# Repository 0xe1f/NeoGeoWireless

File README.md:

NeoGeoWireless
====

NeoGeoWireless is a wireless Neo Geo controller, built on top of a cheap
aftermarket 2.4 GHz SNES Controller.  
It works by converting the SNES controller signals (that would normally go to
the SNES) to format compatible with Neo-Geo, in the process adding features,
like Turbo and Macro button support.

## Requirements

[2.4GHz SNES Controller](https://www.amazon.com/gp/product/B09H4826RV/)  
3x 0.1uF Capacitors  
LED (to display turbo status)  
Atmega328P  
Neo-Geo controller DIN connector, hopefully cannibalized from NG Controller
extension cords  
Custom PCB schematics for the receiver add-on board
([KiCad](schematics/rx-snes/), [PDF](docs/schematic.pdf))  
[3D-printed case](stl/NGRcvrSNES.stl) ([slightly roomier version](stl/NGRcvrSNESDev.stl) for prototyping)  
[Firmware](build/) for the Atmega328P (`make writefuses && make install`)  

## Examples

### Plug front

### SNES receiver board

### Add-on board

### Neo Geo Controller port pinout

### Button mapping

## LICENSE

```
Copyright 2021-2024, Akop Karapetyan

Licensed under the Apache License, Version 2.0 (the "License");
you may not use this file except in compliance with the License.
You may obtain a copy of the License at

    http://www.apache.org/licenses/LICENSE-2.0

Unless required by applicable law or agreed to in writing, software
distributed under the License is distributed on an "AS IS" BASIS,
WITHOUT WARRANTIES OR CONDITIONS OF ANY KIND, either express or implied.
See the License for the specific language governing permissions and
limitations under the License.
```

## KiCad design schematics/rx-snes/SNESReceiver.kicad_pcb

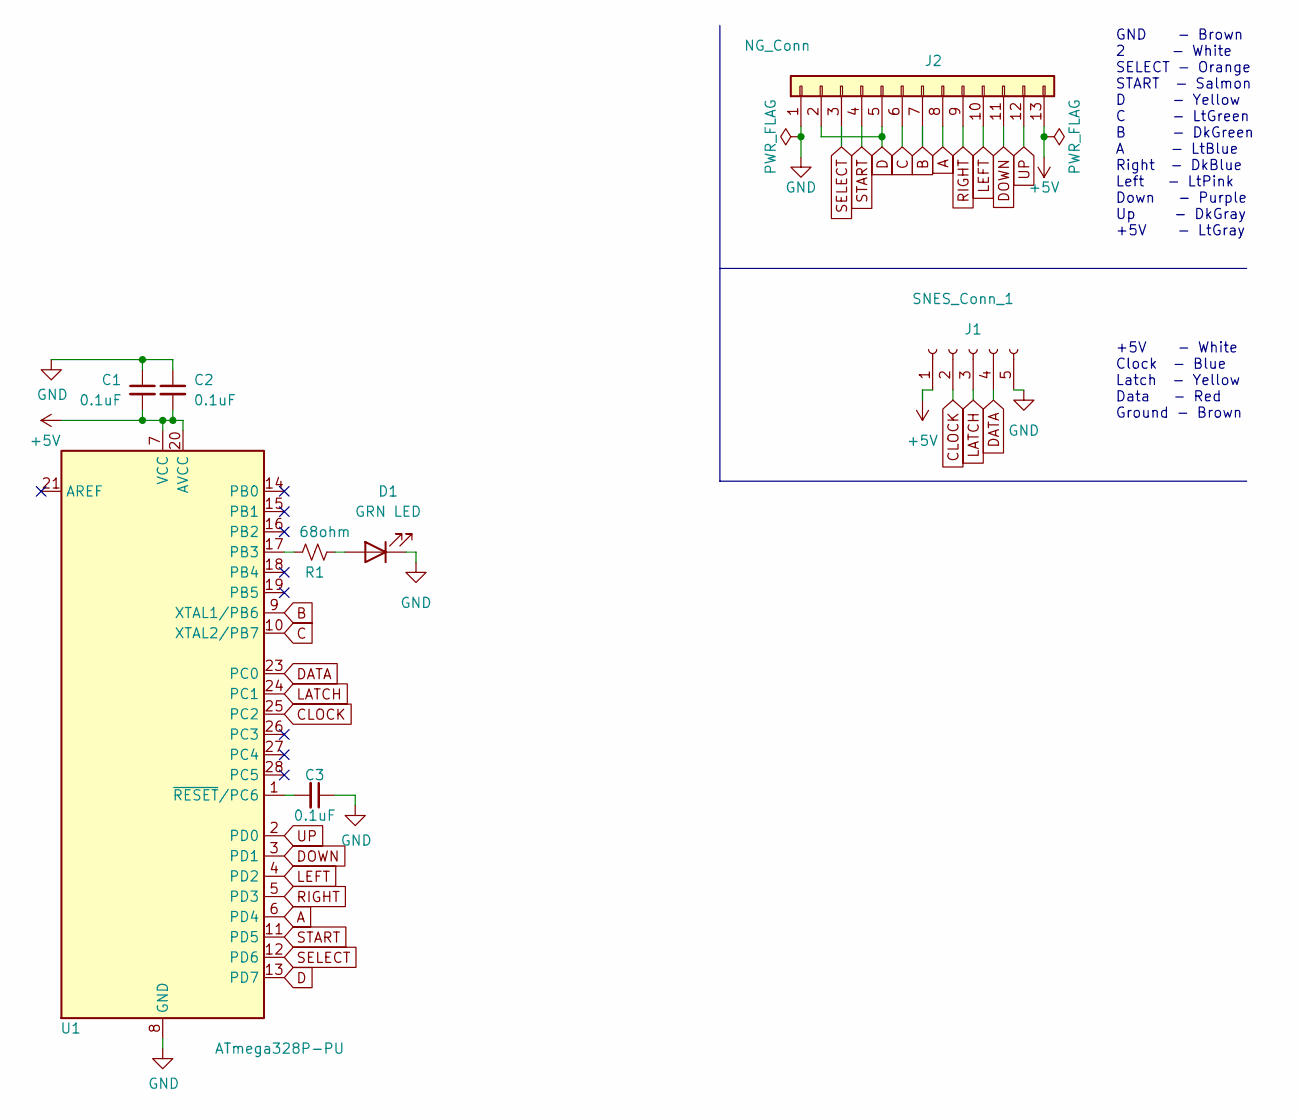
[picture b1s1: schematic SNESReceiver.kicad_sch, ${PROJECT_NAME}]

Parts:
C1, C2, C3: 0.1uF; C_0805_2012Metric_Pad1.18x1.45mm_HandSolder
D1: GRN LED; LED_Rectangular_W3.0mm_H2.0mm
J1: SNES_Conn_1; Wide5PinConnector
J2: NG_Conn; PinHeader_1x13_P2.54mm_Vertical
R1: 68ohm; R_0805_2012Metric_Pad1.20x1.40mm_HandSolder
U1: ATmega328P-PU; DIP-28_W7.62mm

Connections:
+5V: C1.2, C2.2, J1.1, J2.13, U1.7 (VCC), U1.20 (AVCC)
A: J2.8, U1.6 (PD4)
B: J2.7, U1.9 (XTAL1/PB6)
C: J2.6, U1.10 (XTAL2/PB7)
CLOCK: J1.2, U1.25 (PC2)
D: J2.2, J2.5, U1.13 (PD7)
DATA: J1.4, U1.23 (PC0)
DOWN: J2.11, U1.3 (PD1)
GND: C1.1, C2.1, C3.1, D1.1 (K), J1.5, J2.1, U1.8 (GND), U1.22 (GND)
LATCH: J1.3, U1.24 (PC1)
LEFT: J2.10, U1.4 (PD2)
unnamed: C3.2, U1.1 (~RESET/PC6)
unnamed: D1.2 (A), R1.2
unnamed: R1.1, U1.17 (PB3)
RIGHT: J2.9, U1.5 (PD3)
SELECT: J2.3, U1.12 (PD6)
START: J2.4, U1.11 (PD5)
UP: J2.12, U1.2 (PD0)

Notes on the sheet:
+5V - White Clock - Blue Latch - Yellow Data - Red Ground - Brown
GND - Brown 2 - White SELECT - Orange START - Salmon D - Yellow C - LtGreen B - DkGreen A - LtBlue Right - DkBlue Left - LtPink Down - Purple Up - DkGray +5V - LtGray

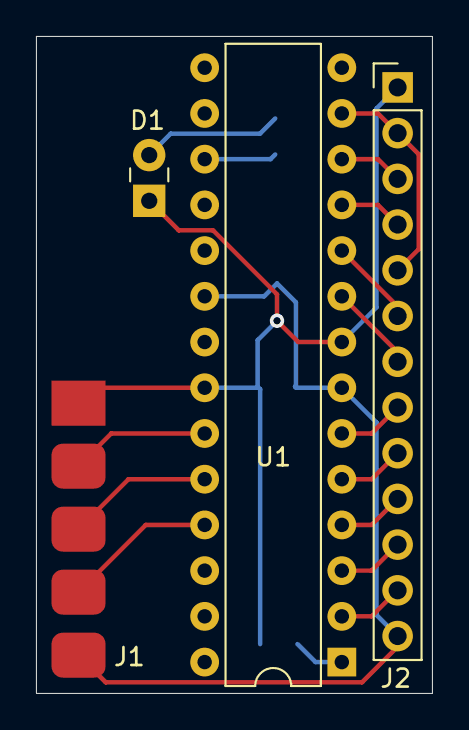
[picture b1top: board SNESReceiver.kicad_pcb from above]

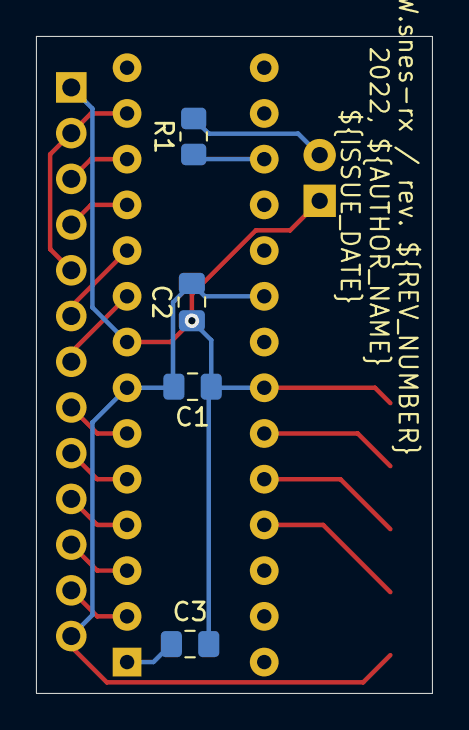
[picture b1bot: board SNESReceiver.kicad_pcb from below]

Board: 2 copper layers, 22.0 x 36.5 mm, 8 parts (4 on the bottom side), 18 nets.

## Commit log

2024-05-12 Add license
